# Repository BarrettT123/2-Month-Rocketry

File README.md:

This project was part of the Space Hardware Club (SHC)'s 2-month program, where we designed built and flew a high power rocket with custom areobrakes, and a custom flight computer. My position on the project was Electrical Team Lead. In this position I was incharge of a small group of people, and we were incharge of the avionics for the rocket, and integrating with the mechanical and software teams. While I mainly was incharge of the design and assembly of the flight computer, I also helped out on the software team a little.

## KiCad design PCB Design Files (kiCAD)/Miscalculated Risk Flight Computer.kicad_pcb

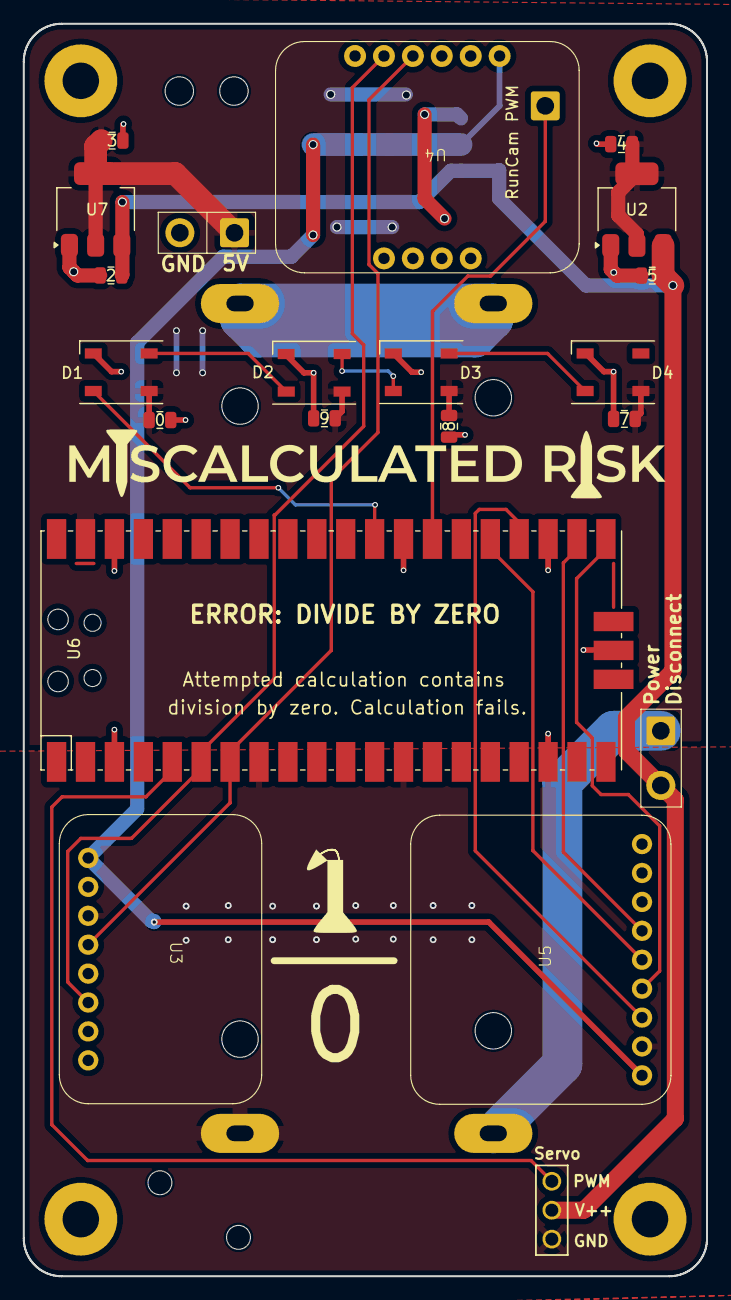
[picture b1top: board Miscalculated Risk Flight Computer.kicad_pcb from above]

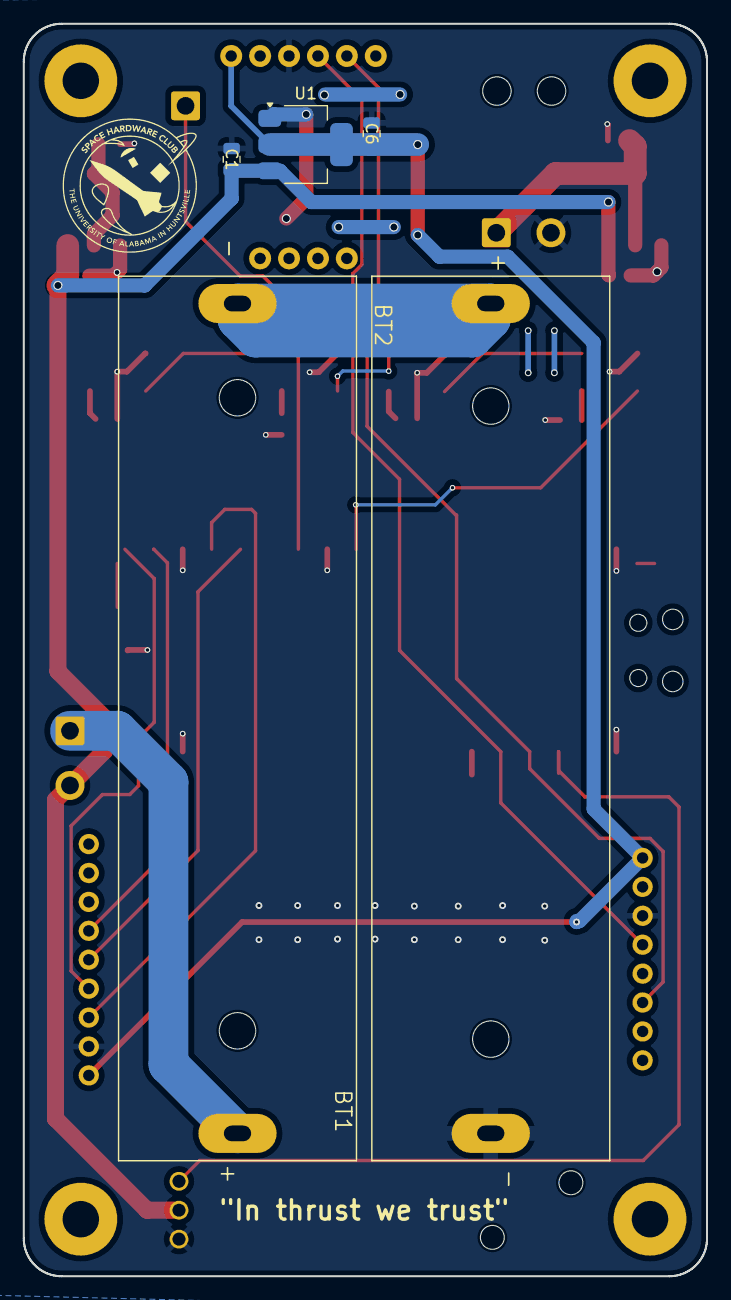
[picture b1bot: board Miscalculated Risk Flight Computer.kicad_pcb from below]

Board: 2 copper layers, 60.0 x 110.0 mm, 27 parts (5 on the bottom side), 18 nets.

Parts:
0, 7, 8, 9: C_Small; C_0805_2012Metric
2, 5: 10u; C_0805_2012Metric
3, 4: 22uF; C_0805_2012Metric
BT1, BT2: 18650; BAT_BH-18650-PC
C1: 10u; C_0805_2012Metric
C6: 22uF; C_0805_2012Metric
CAM1: SolderWire-0.75sqmm_1x02_P4.8mm_D1.25mm_OD2.3mm
D1, D2, D3, D4: WS2812B; LED_WS2812B_PLCC4_5.0x5.0mm_P3.2mm
J1: 61300311121; Servo Pin Header
RunCam PWM: SolderWire-0.75sqmm_1x01_D1.25mm_OD2.3mm
U1: AMS1117-3.3; SOT-223-3_TabPin2
U2, U7: AMS1117-5.0; SOT-223-3_TabPin2
U3: BMP388 Adafruit Breakout
U4: BNO055 Adafruit Breakout
U5: Micro SD Adafruit Breakout
U6: Pi Pico; RPi_Pico_SMD_TH
U9: SolderWire-0.75sqmm_1x02_P4.8mm_D1.25mm_OD2.3mm

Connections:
+3.3V: C6.1, U1.2 (VO), U3.1 (Vin), U4.1 (Vin), U5.1 (3.3V)
+5V: 0.1, 3.1, 4.1, 7.1, 8.1, 9.1, CAM1.1 (5V), D1.1 (VDD), D2.1 (VDD), D3.1 (VDD), D4.1 (VDD), U2.2 (VO), U6.39 (VSYS), U7.2 (VO)
+BATT: 2.1, 5.1, C1.1, J1.2, U1.3 (VI), U2.3 (VI), U7.3 (VI), U9.2 (PWR+)
Airbrake PWM: J1.3, U6.5 (GPIO3)
BATT+Direct: BT2.P, U9.1 (BATT+)
CS: U5.6 (C5), U6.22 (GPIO17)
Camera Control: RunCam PWM.1, U6.27 (GPIO21)
DI: U5.5 (DI), U6.25 (GPIO19)
DO: U5.4 (DO), U6.21 (GPIO16)
GND: 0.2, 2.2, 3.2, 4.2, 5.2, 7.2, 8.2, 9.2, BT1.N, C1.2, C6.2, CAM1.2 (GND), D1.3 (VSS), D2.3 (VSS), D3.3 (VSS), D4.3 (VSS), J1.1, U1.1 (GND), U2.1 (GND), U3.3 (GND), U4.3 (GND), U5.2 (GND), U6.3 (GND), U6.8 (GND), U6.13 (GND), U6.18 (GND), U6.23 (GND), U6.28 (GND), U6.38 (GND), U6.42 (GND), U7.1 (GND)
NeoPixels: D1.4 (DIN), U6.29 (GPIO22)
unnamed: BT1.P, BT2.N
unnamed: D1.2 (DOUT), D2.4 (DIN)
unnamed: D2.2 (DOUT), D3.4 (DIN)
unnamed: D3.2 (DOUT), D4.4 (DIN)
SCL: U3.4 (SCL), U4.4 (SCL), U6.7 (GPIO5)
SCLK: U5.3 (SCLK), U6.24 (GPIO18)
SDA: U3.6 (SDA), U4.5 (SDA), U6.6 (GPIO4)

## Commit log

2025-02-18 Flight Software for Flight Computer
2025-02-18 Schematic and PCB Design Files for Flight Computer
2025-02-18 CAD Assembly of Flight Computers and Mounting
2025-02-18 CAD of Flight Computer PCB
2025-02-18 Photos of Flight Computer PCB Copper Layers
2025-02-18 Change Folder Name
2025-02-18 3D Renderings of Assembled Flight Computer
